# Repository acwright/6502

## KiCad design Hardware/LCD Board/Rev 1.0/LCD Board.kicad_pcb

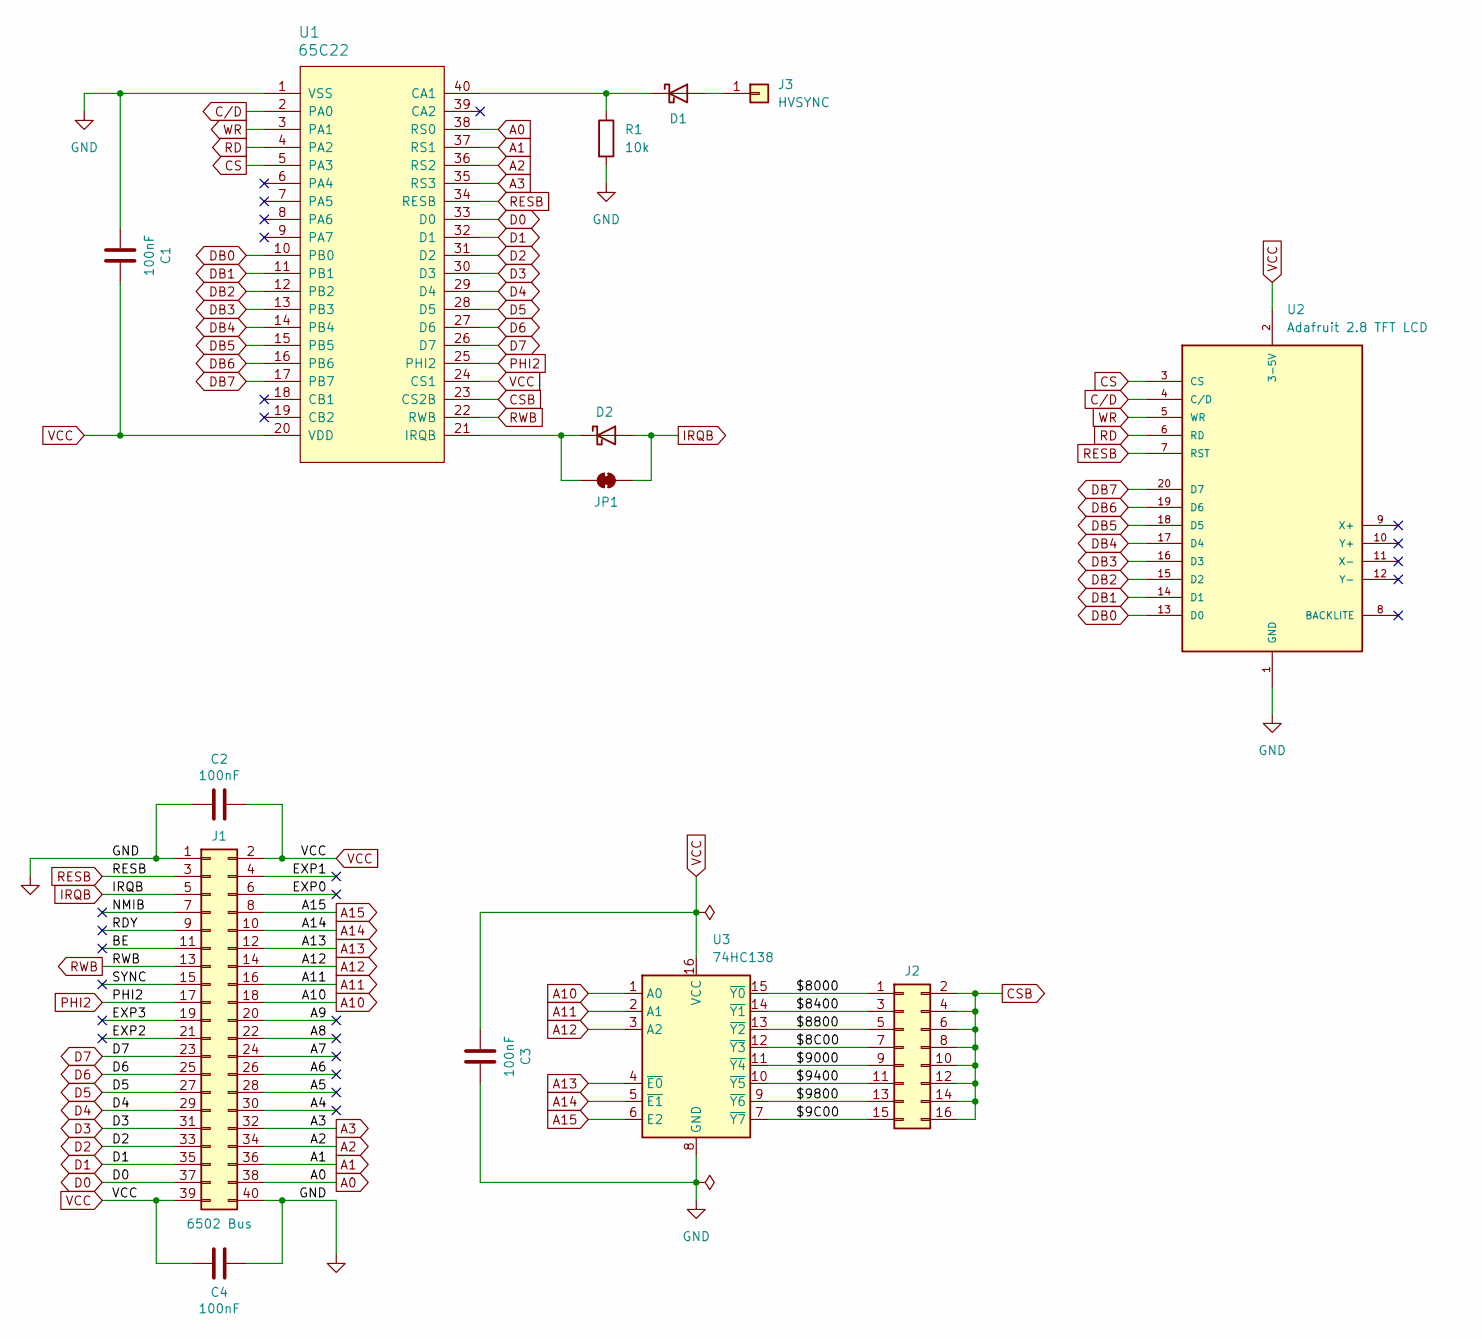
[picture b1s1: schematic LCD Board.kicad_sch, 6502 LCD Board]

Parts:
C1, C2, C3, C4: 100nF; C_Disc_D5.0mm_W2.5mm_P2.50mm
D1, D2: D_Schottky; D_DO-35_SOD27_P7.62mm_Horizontal
J1: 6502 Bus; 6502 Bus Connector
J2: Conn_02x08_Odd_Even; PinHeader_2x08_P2.54mm_Vertical
J3: HVSYNC; PinHeader_1x01_P2.54mm_Vertical
JP1: SolderJumper_2_Bridged; SolderJumper-2_P1.3mm_Bridged_RoundedPad1.0x1.5mm
R1: 10k; R_Axial_DIN0204_L3.6mm_D1.6mm_P5.08mm_Horizontal
U1: 65C22; DIP-40_W15.24mm_Socket_LongPads
U2: Adafruit 2.8 TFT LCD; PARTREV 2025-02-10
U3: 74HC138; DIP-16_W7.62mm_Socket_LongPads

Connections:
/$8C00: J2.7, U3.12 (~Y3)
/$9C00: J2.15, U3.7 (~Y7)
/$8000: J2.1, U3.15 (~Y0)
/$8400: J2.3, U3.14 (~Y1)
/$8800: J2.5, U3.13 (~Y2)
/$9000: J2.9, U3.11 (~Y4)
/$9400: J2.11, U3.10 (~Y5)
/$9800: J2.13, U3.9 (~Y6)
/A4: J1.30
/A5: J1.28
/A6: J1.26
/A7: J1.24
/A8: J1.22
/A9: J1.20
/BE: J1.11
/EXP0: J1.6
/EXP1: J1.4
/EXP2: J1.21
/EXP3: J1.19
/NMIB: J1.7
/RDY: J1.9
/SYNC: J1.15
A0: J1.38, U1.38 (RS0)
A1: J1.36, U1.37 (RS1)
A2: J1.34, U1.36 (RS2)
A3: J1.32, U1.35 (RS3)
A10: J1.18, U3.1 (A0)
A11: J1.16, U3.2 (A1)
A12: J1.14, U3.3 (A2)
A13: J1.12, U3.4 (~E0)
A14: J1.10, U3.5 (~E1)
A15: J1.8, U3.6 (E2)
CS: U1.5 (PA3), U2.3 (CS)
CSB: J2.2, J2.4, J2.6, J2.8, J2.10, J2.12, J2.14, J2.16, U1.23 (CS2B)
C/D: U1.2 (PA0), U2.4 (C/D)
D0: J1.37, U1.33 (D0)
D1: J1.35, U1.32 (D1)
D2: J1.33, U1.31 (D2)
D3: J1.31, U1.30 (D3)
D4: J1.29, U1.29 (D4)
D5: J1.27, U1.28 (D5)
D6: J1.25, U1.27 (D6)
D7: J1.23, U1.26 (D7)
DB0: U1.10 (PB0), U2.13 (D0)
DB1: U1.11 (PB1), U2.14 (D1)
DB2: U1.12 (PB2), U2.15 (D2)
DB3: U1.13 (PB3), U2.16 (D3)
DB4: U1.14 (PB4), U2.17 (D4)
DB5: U1.15 (PB5), U2.18 (D5)
DB6: U1.16 (PB6), U2.19 (D6)
DB7: U1.17 (PB7), U2.20 (D7)
GND: C1.1, C2.2, C3.2, C4.1, J1.1, J1.40, R1.2, U1.1 (VSS), U2.1 (GND), U3.8 (GND)
IRQB: D2.2 (A), J1.5, JP1.2 (B)
unnamed: D1.2 (A), J3.1
unnamed: D1.1 (K), R1.1, U1.40 (CA1)
unnamed: D2.1 (K), JP1.1 (A), U1.21 (IRQB)
PHI2: J1.17, U1.25 (PHI2)
RD: U1.4 (PA2), U2.6 (RD)
RESB: J1.3, U1.34 (RESB), U2.7 (RST)
RWB: J1.13, U1.22 (RWB)
VCC: C1.2, C2.1, C3.1, C4.2, J1.2, J1.39, U1.20 (VDD), U1.24 (CS1), U2.2 (3-5V), U3.16 (VCC)
WR: U1.3 (PA1), U2.5 (WR)

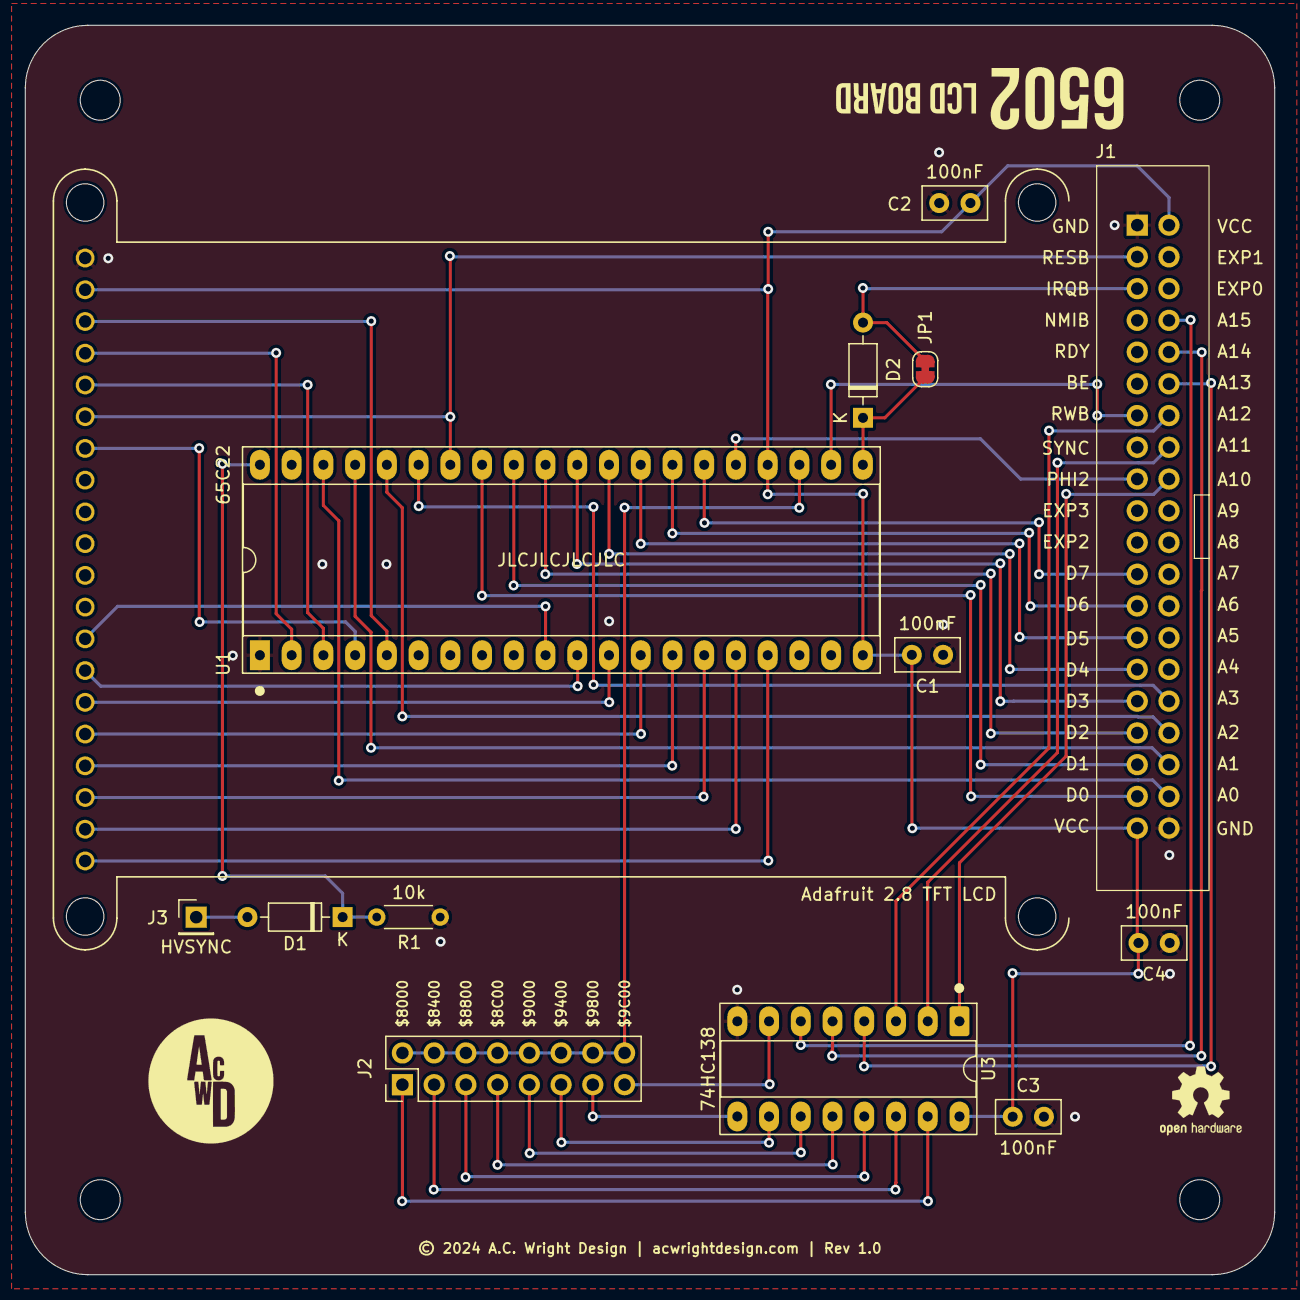
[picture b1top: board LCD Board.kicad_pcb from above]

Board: 2 copper layers, 100.0 x 100.0 mm, 18 parts (0 on the bottom side), 48 nets.

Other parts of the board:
H1, H2, H3, H4: MountingHole; MountingHole_3.2mm_M3

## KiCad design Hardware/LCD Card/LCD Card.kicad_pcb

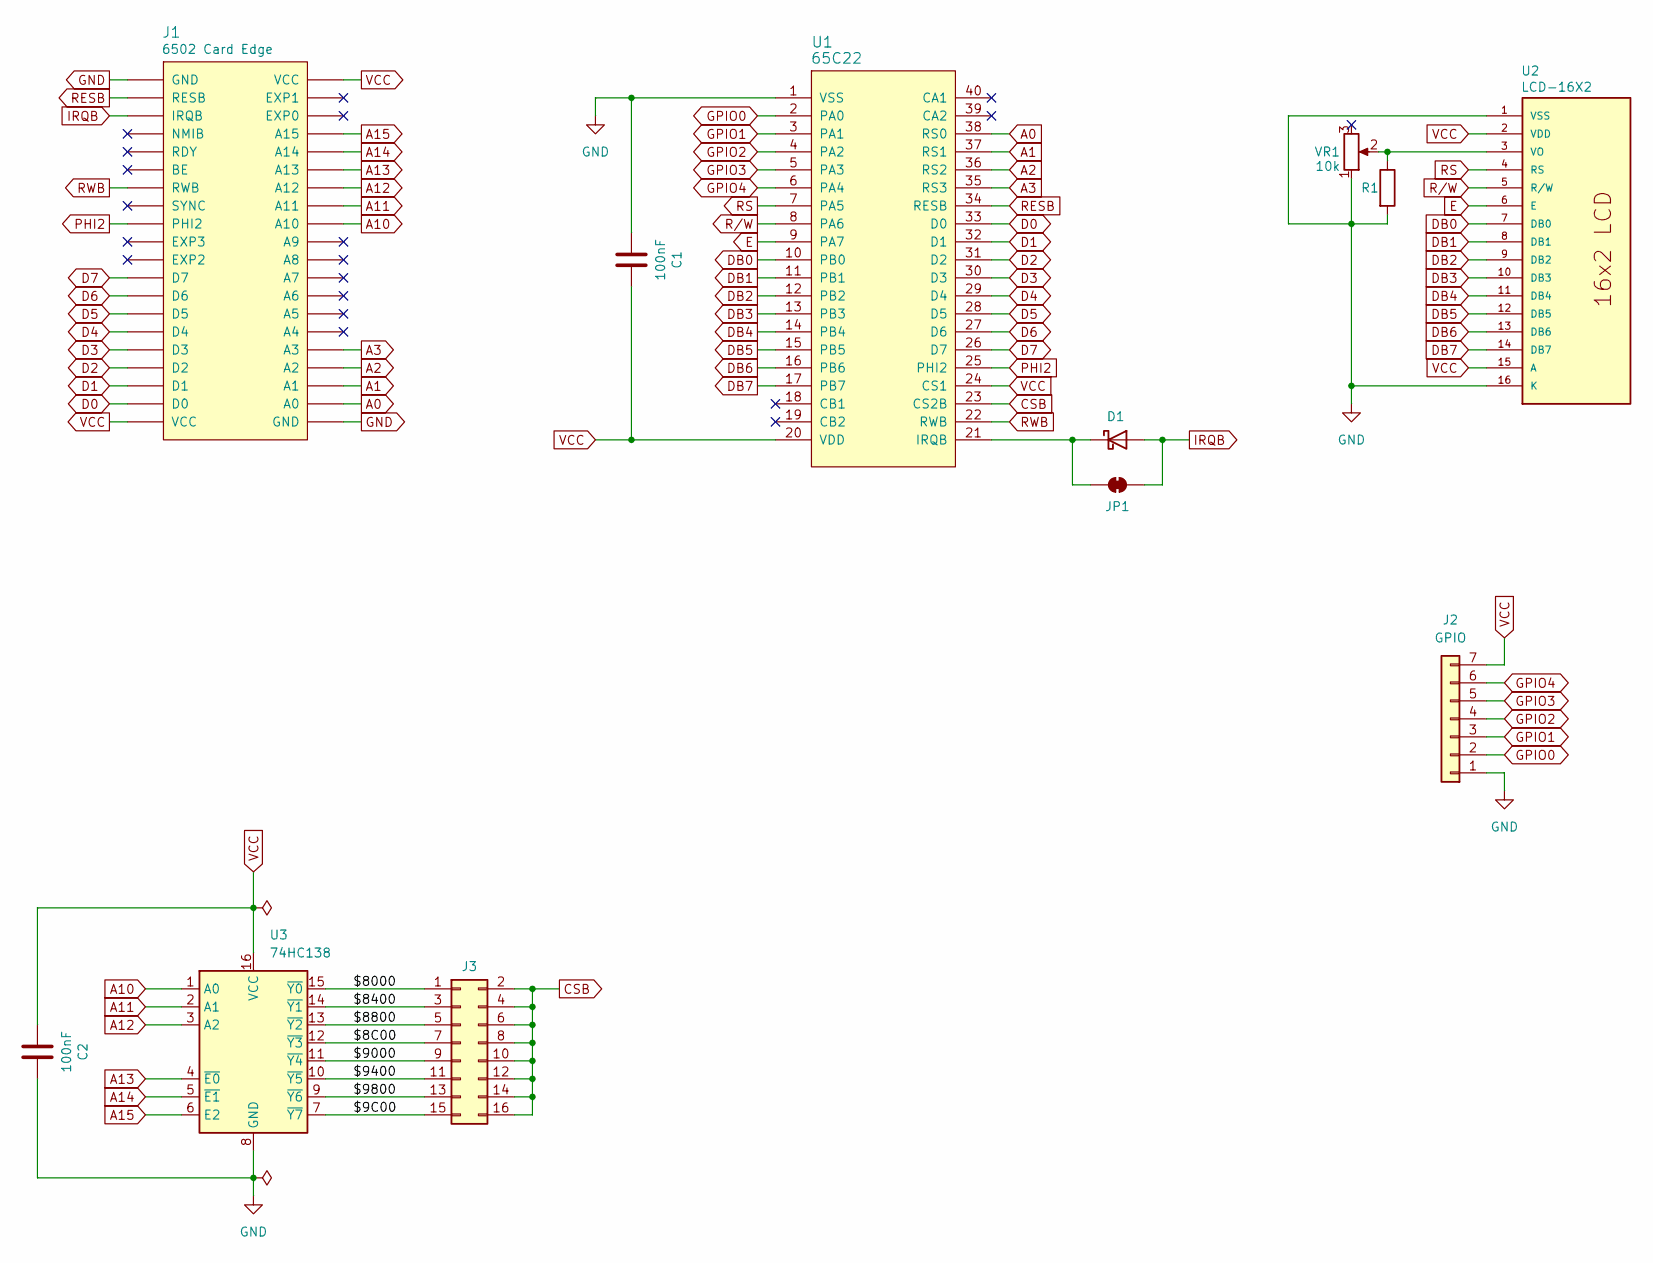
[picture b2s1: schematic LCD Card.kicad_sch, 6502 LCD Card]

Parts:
C1, C2: 100nF; C_0805_2012Metric; LCSC C49678
D1: D_Schottky; D_DO-35_SOD27_P7.62mm_Horizontal
J1: 6502 Card Edge
J2: GPIO; PinHeader_1x07_P2.54mm_Horizontal
J3: Conn_02x08_Odd_Even; PinHeader_2x08_P2.54mm_Vertical
JP1: SolderJumper_2_Bridged; SolderJumper-2_P1.3mm_Bridged_RoundedPad1.0x1.5mm
R1: R; R_Axial_DIN0204_L3.6mm_D1.6mm_P5.08mm_Horizontal
U1: 65C22; DIP-40_W15.24mm_Socket_LongPads
U2: LCD-16X2; PARTREV N/A
U3: 74HC138; SOIC-16_3.9x9.9mm_P1.27mm; LCSC C5602
VR1: 10k; 3386F-1-103TLF

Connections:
/$8C00: J3.7, U3.12 (~Y3)
/$9C00: J3.15, U3.7 (~Y7)
/$8000: J3.1, U3.15 (~Y0)
/$8400: J3.3, U3.14 (~Y1)
/$8800: J3.5, U3.13 (~Y2)
/$9000: J3.9, U3.11 (~Y4)
/$9400: J3.11, U3.10 (~Y5)
/$9800: J3.13, U3.9 (~Y6)
A0: J1.A0, U1.38 (RS0)
A1: J1.A1, U1.37 (RS1)
A2: J1.A2, U1.36 (RS2)
A3: J1.A3, U1.35 (RS3)
A10: J1.A10, U3.1 (A0)
A11: J1.A11, U3.2 (A1)
A12: J1.A12, U3.3 (A2)
A13: J1.A13, U3.4 (~E0)
A14: J1.A14, U3.5 (~E1)
A15: J1.A15, U3.6 (E2)
CSB: J3.2, J3.4, J3.6, J3.8, J3.10, J3.12, J3.14, J3.16, U1.23 (CS2B)
D0: J1.D0, U1.33 (D0)
D1: J1.D1, U1.32 (D1)
D2: J1.D2, U1.31 (D2)
D3: J1.D3, U1.30 (D3)
D4: J1.D4, U1.29 (D4)
D5: J1.D5, U1.28 (D5)
D6: J1.D6, U1.27 (D6)
D7: J1.D7, U1.26 (D7)
DB0: U1.10 (PB0), U2.7 (DB0)
DB1: U1.11 (PB1), U2.8 (DB1)
DB2: U1.12 (PB2), U2.9 (DB2)
DB3: U1.13 (PB3), U2.10 (DB3)
DB4: U1.14 (PB4), U2.11 (DB4)
DB5: U1.15 (PB5), U2.12 (DB5)
DB6: U1.16 (PB6), U2.13 (DB6)
DB7: U1.17 (PB7), U2.14 (DB7)
E: U1.9 (PA7), U2.6 (E)
GND: C1.1, C2.2, J1.GND, J2.1, R1.2, U1.1 (VSS), U2.1 (VSS), U2.16 (K), U3.8 (GND), VR1.1
GPIO0: J2.2, U1.2 (PA0)
GPIO1: J2.3, U1.3 (PA1)
GPIO2: J2.4, U1.4 (PA2)
GPIO3: J2.5, U1.5 (PA3)
GPIO4: J2.6, U1.6 (PA4)
IRQB: D1.2 (A), J1.IRQB, JP1.2 (B)
unnamed: D1.1 (K), JP1.1 (A), U1.21 (IRQB)
unnamed: R1.1, U2.3 (VO), VR1.2
PHI2: J1.PHI2, U1.25 (PHI2)
RESB: J1.RESB, U1.34 (RESB)
RS: U1.7 (PA5), U2.4 (RS)
RWB: J1.RWB, U1.22 (RWB)
R/W: U1.8 (PA6), U2.5 (R/W)
VCC: C1.2, C2.1, J1.VCC, J2.7, U1.20 (VDD), U1.24 (CS1), U2.2 (VDD), U2.15 (A), U3.16 (VCC)

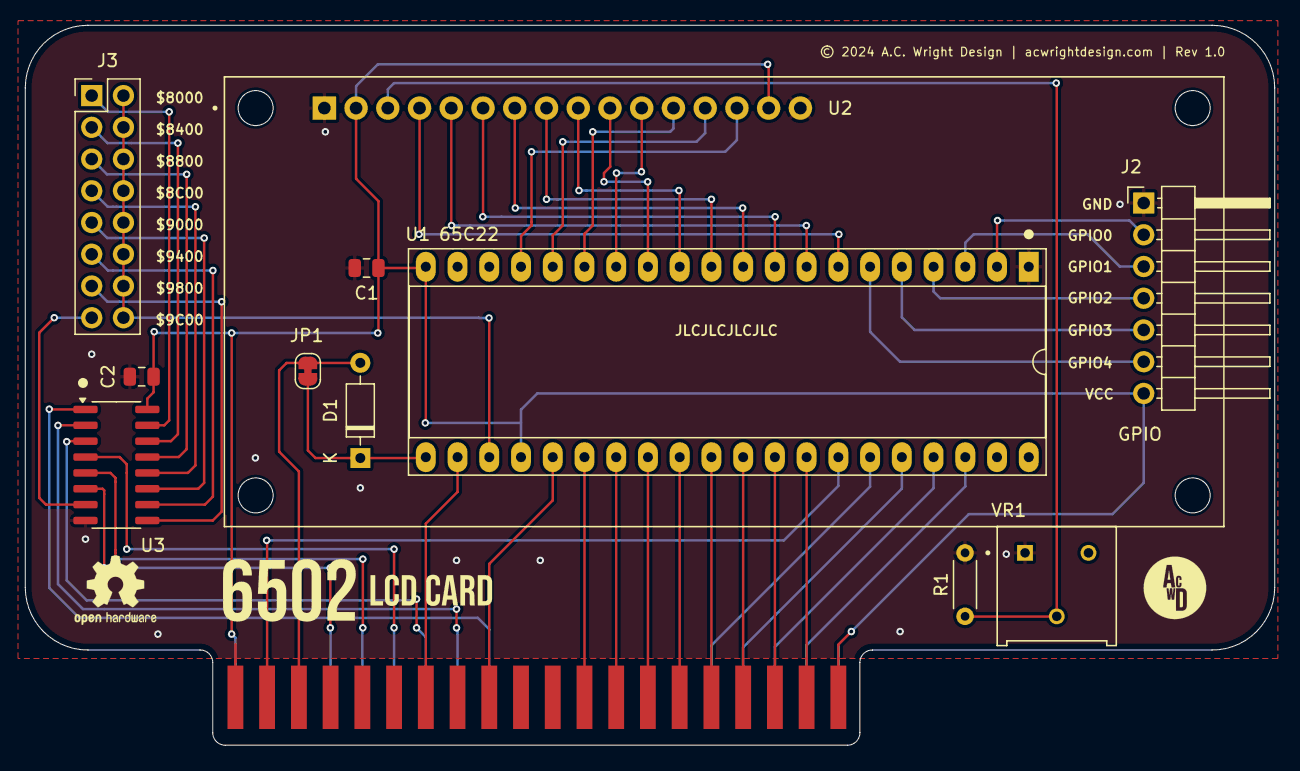
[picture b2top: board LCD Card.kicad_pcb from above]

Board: 2 copper layers, 100.0 x 57.6 mm, 12 parts (0 on the bottom side), 51 nets.

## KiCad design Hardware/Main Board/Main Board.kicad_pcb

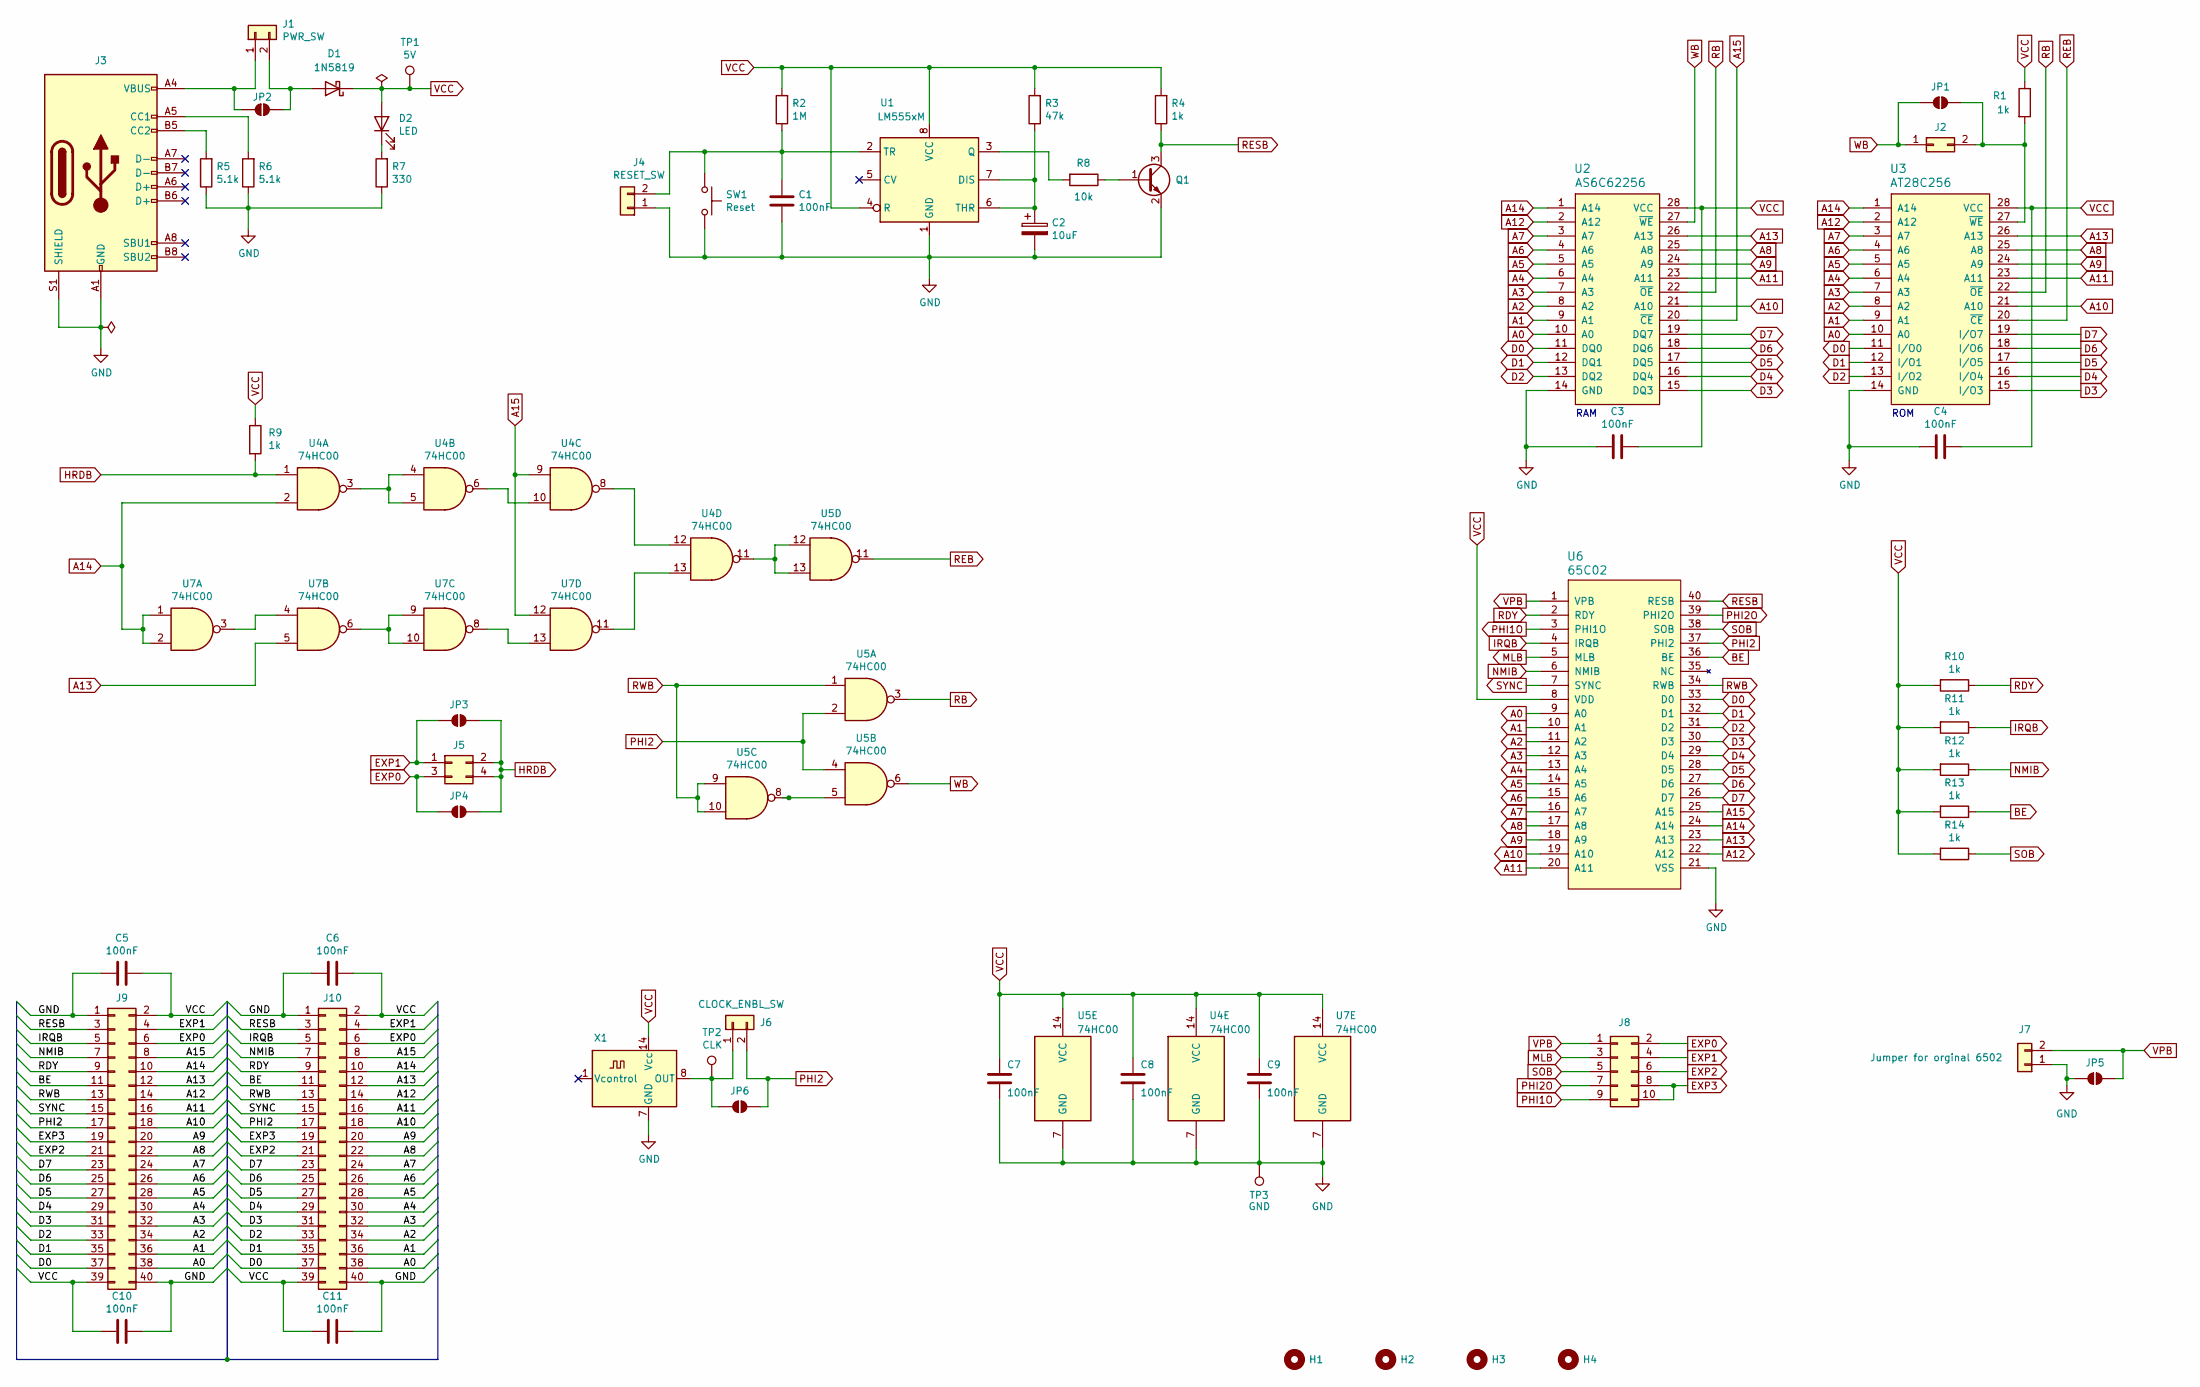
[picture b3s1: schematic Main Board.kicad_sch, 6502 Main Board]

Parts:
C1, C3, C4, C5, C6, C7, C8, C9, C10, C11: 100nF; C_0805_2012Metric; LCSC C49678
C2: 10uF; C_1206_3216Metric; LCSC C7171
D1: 1N5819; D_SOD-323F; LCSC C191023
D2: LED; LED_0805_2012Metric; LCSC C2297
H1, H2, H3, H4: MountingHole; MountingHole_3.2mm_M3
J1: PWR_SW; JST_XH_B2B-XH-A_1x02_P2.50mm_Vertical; Digikey 455-2247-ND
J2: Conn_02x01; PinHeader_1x02_P2.54mm_Vertical
J3: USB_C_Receptacle_USB2.0; USB_C_Receptacle_HRO_TYPE-C-31-M-12; LCSC C2988369
J4: RESET_SW; JST_XH_B2B-XH-A_1x02_P2.50mm_Vertical; Digikey 455-2247-ND
J5: Conn_02x02_Odd_Even; PinHeader_2x02_P2.54mm_Vertical
J6: CLOCK_ENBL_SW; JST_XH_B2B-XH-A_1x02_P2.50mm_Vertical; Digikey 455-2247-ND
J7: Conn_01x02; PinHeader_1x02_P2.54mm_Vertical
J8: Conn_02x05_Odd_Even; PinHeader_2x05_P2.54mm_Vertical
J9: Conn_02x20_Odd_Even; RHDR40W82P485X254_2X20_5740X93; Mouser 571-5-5530843-4
J10: Conn_02x20_Odd_Even; PinHeader_2x20_P2.54mm_Vertical
JP1, JP2, JP3, JP4, JP5, JP6: SolderJumper_2_Open; SolderJumper-2_P1.3mm_Open_RoundedPad1.0x1.5mm
Q1: Q_NPN_BEC; SOT-23; LCSC C2150
R1, R4, R9, R10, R11, R12, R13, R14: 1k; R_0805_2012Metric; LCSC C17513
R2: 1M; R_0805_2012Metric; LCSC C17514
R3: 47k; R_0805_2012Metric; LCSC C17713
R5, R6: 5.1k; R_0805_2012Metric; LCSC C27834
R7: 330; R_0805_2012Metric; LCSC C17630
R8: 10k; R_0805_2012Metric; LCSC C17414
SW1: Reset; SW_TS-1187A-B-A-B; LCSC C318884
TP1: 5V; TestPoint_Pad_1.0x1.0mm
TP2: CLK; TestPoint_Pad_1.0x1.0mm
TP3: GND; TestPoint_Pad_1.0x1.0mm
U1: LM555xM; SOIC-8_3.9x4.9mm_P1.27mm; LCSC C7593
U2: AS6C62256; DIP-28_W15.24mm_Socket_LongPads
U3: AT28C256; DIP_Socket-28_W11.9_W12.7_W15.24_W17.78_W18.5_3M_228-1277-0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
U4, U5, U7: 74HC00; SOIC-14_3.9x8.7mm_P1.27mm; LCSC C5586
U6: 65C02; DIP-40_W15.24mm_Socket_LongPads
X1: OCXO-14; Oscillator_DIP-14

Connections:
A0: J9.38, J10.38, U2.10 (A0), U3.10 (A0), U6.9 (A0)
A1: J9.36, J10.36, U2.9 (A1), U3.9 (A1), U6.10 (A1)
A2: J9.34, J10.34, U2.8 (A2), U3.8 (A2), U6.11 (A2)
A3: J9.32, J10.32, U2.7 (A3), U3.7 (A3), U6.12 (A3)
A4: J9.30, J10.30, U2.6 (A4), U3.6 (A4), U6.13 (A4)
A5: J9.28, J10.28, U2.5 (A5), U3.5 (A5), U6.14 (A5)
A6: J9.26, J10.26, U2.4 (A6), U3.4 (A6), U6.15 (A6)
A7: J9.24, J10.24, U2.3 (A7), U3.3 (A7), U6.16 (A7)
A8: J9.22, J10.22, U2.25 (A8), U3.25 (A8), U6.17 (A8)
A9: J9.20, J10.20, U2.24 (A9), U3.24 (A9), U6.18 (A9)
A10: J9.18, J10.18, U2.21 (A10), U3.21 (A10), U6.19 (A10)
A11: J9.16, J10.16, U2.23 (A11), U3.23 (A11), U6.20 (A11)
A12: J9.14, J10.14, U2.2 (A12), U3.2 (A12), U6.22 (A12)
A13: J9.12, J10.12, U2.26 (A13), U3.26 (A13), U6.23 (A13), U7.5
A14: J9.10, J10.10, U2.1 (A14), U3.1 (A14), U4.2, U6.24 (A14), U7.1, U7.2
A15: J9.8, J10.8, U2.20 (~CE), U4.9, U6.25 (A15), U7.12
BE: J9.11, J10.11, R13.1, U6.36 (BE)
D0: J9.37, J10.37, U2.11 (DQ0), U3.11 (I/O0), U6.33 (D0)
D1: J9.35, J10.35, U2.12 (DQ1), U3.12 (I/O1), U6.32 (D1)
D2: J9.33, J10.33, U2.13 (DQ2), U3.13 (I/O2), U6.31 (D2)
D3: J9.31, J10.31, U2.15 (DQ3), U3.15 (I/O3), U6.30 (D3)
D4: J9.29, J10.29, U2.16 (DQ4), U3.16 (I/O4), U6.29 (D4)
D5: J9.27, J10.27, U2.17 (DQ5), U3.17 (I/O5), U6.28 (D5)
D6: J9.25, J10.25, U2.18 (DQ6), U3.18 (I/O6), U6.27 (D6)
D7: J9.23, J10.23, U2.19 (DQ7), U3.19 (I/O7), U6.26 (D7)
EXP0: J5.3, J8.2, J9.6, J10.6, JP4.1 (A)
EXP1: J5.1, J8.4, J9.4, J10.4, JP3.1 (A)
EXP2: J8.6, J9.21, J10.21
EXP3: J8.8, J8.10, J9.19, J10.19
GND: C1.2, C2.2, C3.2, C4.2, C5.2, C6.2, C7.2, C8.2, C9.2, C10.1, C11.1, J3.A1 (GND), J3.A12 (GND), J3.B1 (GND), J3.B12 (GND), J3.S1 (SHIELD), J4.1, J7.1, J9.1, J9.40, J10.1, J10.40, JP5.1 (A), Q1.2 (E), R5.1, R6.1, R7.1, SW1.2, TP3.1, U1.1 (GND), U2.14 (GND), U3.14 (GND), U4.7 (GND), U5.7 (GND), U6.21 (VSS), U7.7 (GND), X1.7 (GND)
HRDB: J5.2, J5.4, JP3.2 (B), JP4.2 (B), R9.2, U4.1
IRQB: J9.5, J10.5, R11.1, U6.4 (IRQB)
MLB: J8.3, U6.5 (MLB)
NMIB: J9.7, J10.7, R12.1, U6.6 (NMIB)
unnamed: D1.2 (A), J1.2, JP2.2 (B)
unnamed: D2.1 (K), R7.2
unnamed: J1.1, J3.A4 (VBUS), J3.A9 (VBUS), J3.B4 (VBUS), J3.B9 (VBUS), JP2.1 (A)
unnamed: J2.2, JP1.2 (B), R1.2, U3.27 (~WE)
unnamed: J3.A5 (CC1), R6.2
unnamed: J3.B5 (CC2), R5.2
unnamed: C1.1, J4.2, R2.1, SW1.1, U1.2 (TR)
unnamed: J6.1, JP6.1 (A), TP2.1, X1.8 (OUT)
unnamed: Q1.1 (B), R8.1
unnamed: C2.1, R3.1, U1.6 (THR), U1.7 (DIS)
unnamed: R8.2, U1.3 (Q)
unnamed: U4.3, U4.4, U4.5
unnamed: U4.6, U4.10
unnamed: U4.11, U5.12, U5.13
unnamed: U4.8, U4.12
unnamed: U4.13, U7.11
unnamed: U5.5, U5.8
unnamed: U7.3, U7.4
unnamed: U7.6, U7.9, U7.10
unnamed: U7.8, U7.13
PHI1O: J8.9, U6.3 (PHI1O)
PHI2: J6.2, J9.17, J10.17, JP6.2 (B), U5.2, U5.4, U6.37 (PHI2)
PHI2O: J8.7, U6.39 (PHI2O)
RB: U2.22 (~OE), U3.22 (~OE), U5.3
RDY: J9.9, J10.9, R10.1, U6.2 (RDY)
REB: U3.20 (~CE), U5.11
RESB: J9.3, J10.3, Q1.3 (C), R4.1, U6.40 (RESB)
RWB: J9.13, J10.13, U5.1, U5.9, U5.10, U6.34 (RWB)
SOB: J8.5, R14.1, U6.38 (SOB)
SYNC: J9.15, J10.15, U6.7 (SYNC)
VCC: C3.1, C4.1, C5.1, C6.1, C7.1, C8.1, C9.1, C10.2, C11.2, D1.1 (K), D2.2 (A), J9.2, J9.39, J10.2, J10.39, R1.1, R2.2, R3.2, R4.2, R9.1, R10.2, R11.2, R12.2, R13.2, R14.2, TP1.1, U1.4 (R), U1.8 (VCC), U2.28 (VCC), U3.28 (VCC), U4.14 (VCC), U5.14 (VCC), U6.8 (VDD), U7.14 (VCC), X1.14 (Vcc)
VPB: J7.2, J8.1, JP5.2 (B), U6.1 (VPB)
WB: J2.1, JP1.1 (A), U2.27 (~WE), U5.6

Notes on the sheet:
ROM
RAM

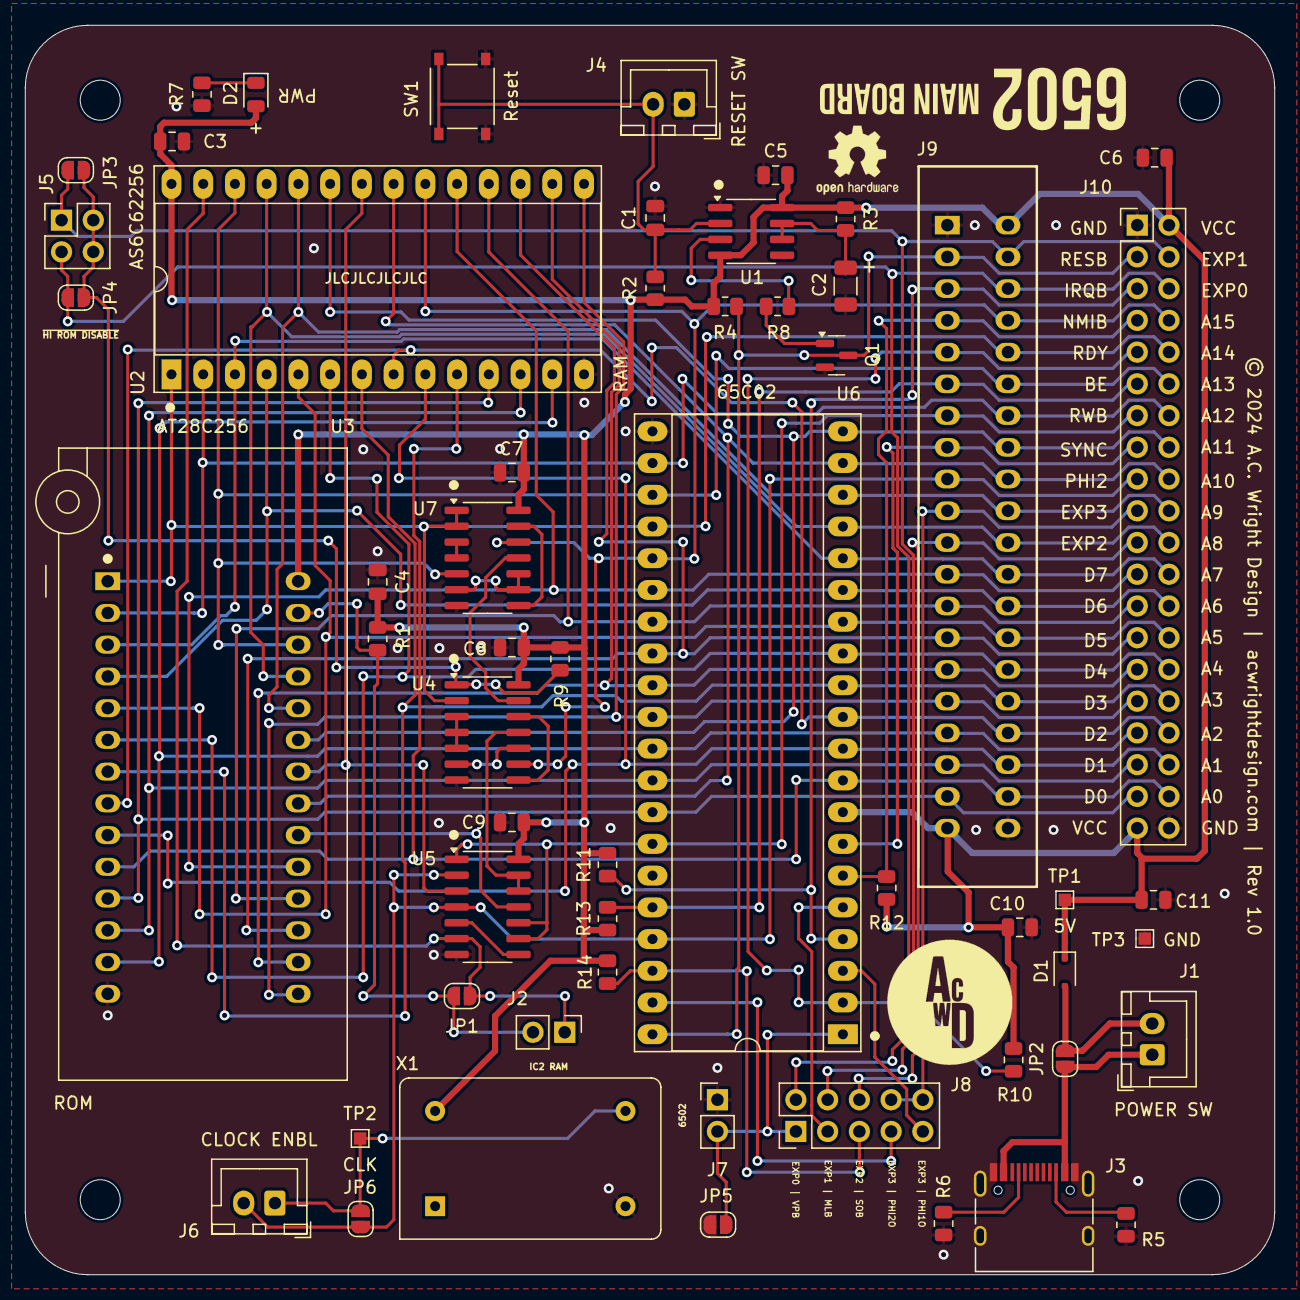
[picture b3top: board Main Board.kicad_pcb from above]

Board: 2 copper layers, 100.0 x 100.0 mm, 60 parts (0 on the bottom side), 67 nets.

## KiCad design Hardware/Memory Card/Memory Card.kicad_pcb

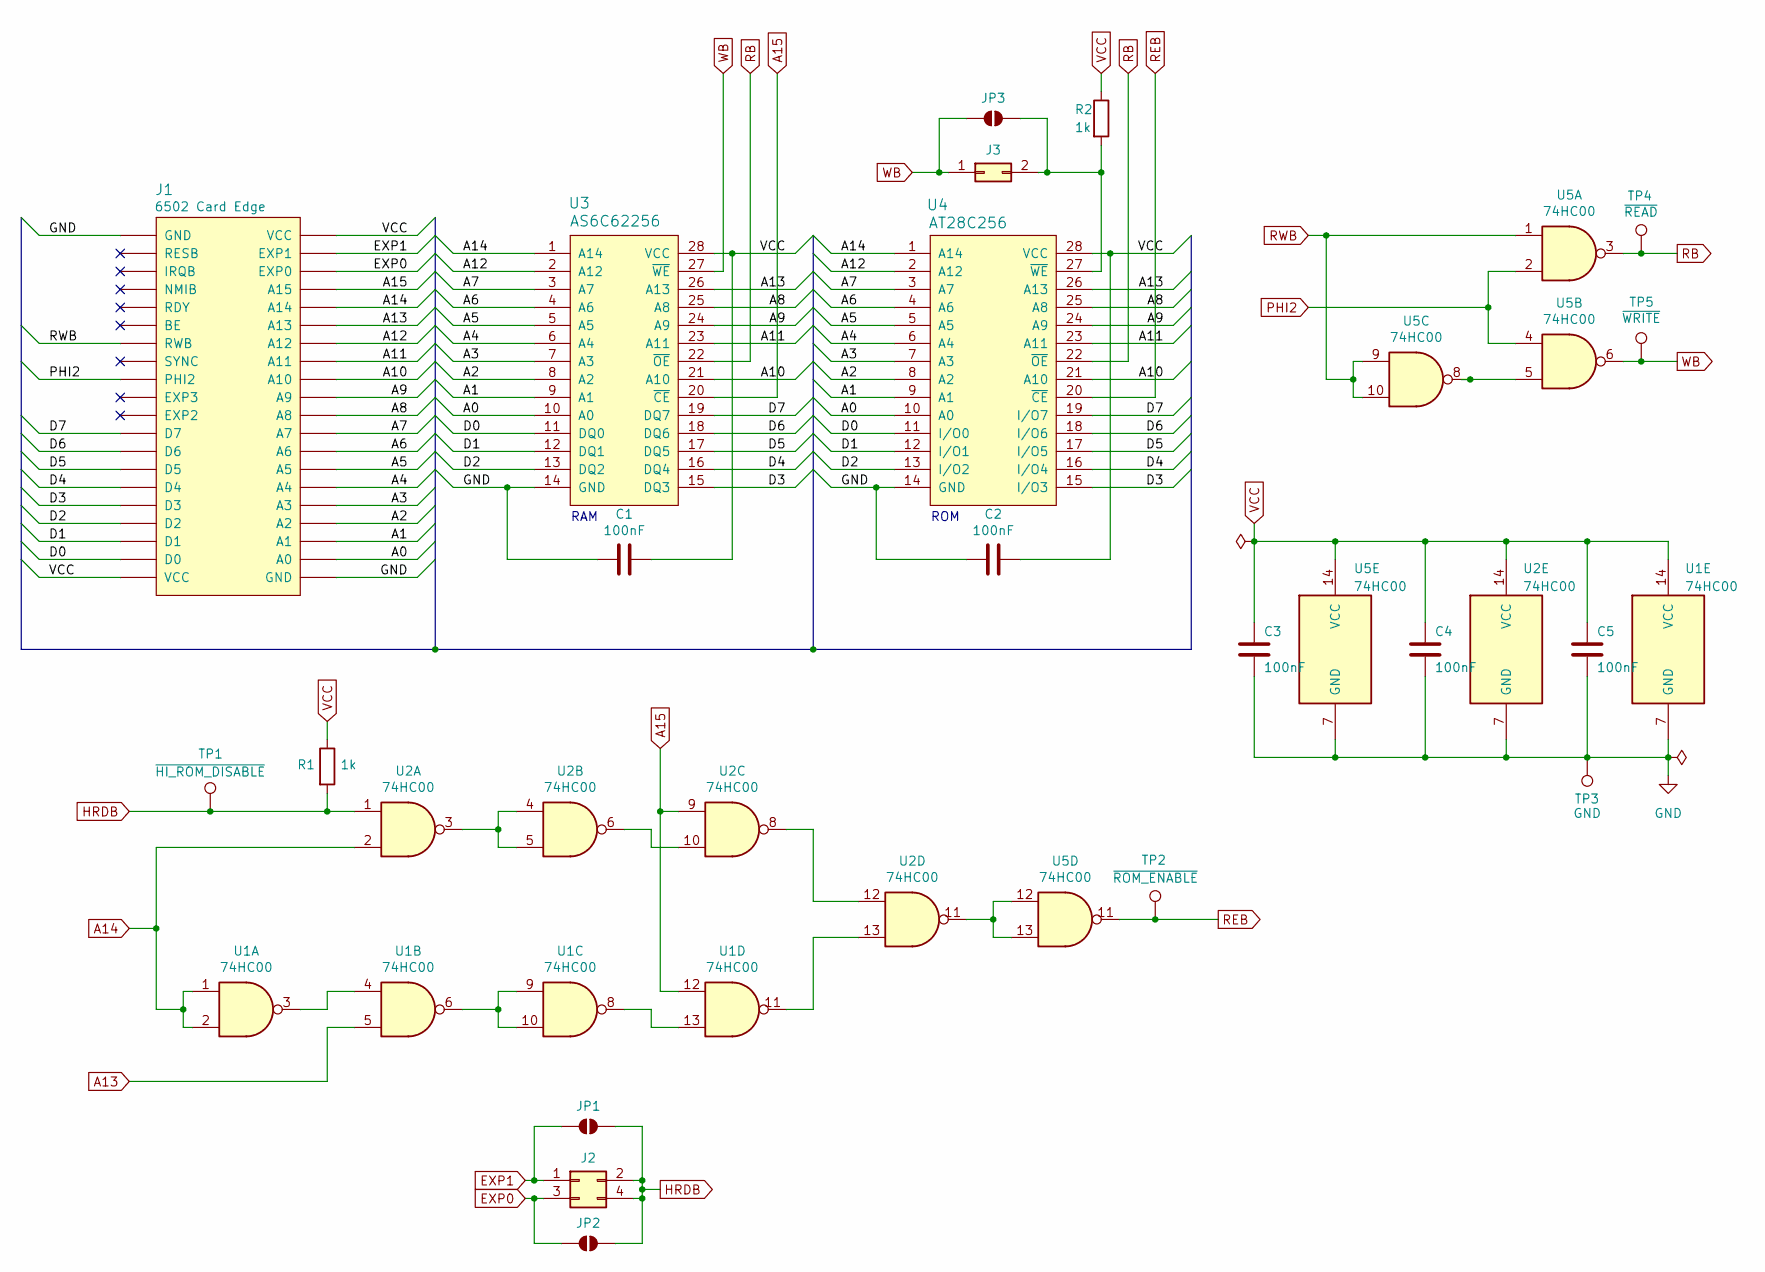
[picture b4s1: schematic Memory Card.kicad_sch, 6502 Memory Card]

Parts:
C1, C2, C3, C4, C5: 100nF; C_0805_2012Metric; LCSC C49678
J1: 6502 Card Edge
J2: Conn_02x02_Odd_Even; PinHeader_2x02_P2.54mm_Vertical
J3: Conn_02x01; PinHeader_1x02_P2.54mm_Vertical
JP1, JP2, JP3: SolderJumper_2_Open; SolderJumper-2_P1.3mm_Open_RoundedPad1.0x1.5mm
R1, R2: 1k; R_0805_2012Metric; LCSC C17513
TP1: ~{HI_ROM_DISABLE}; TestPoint_Pad_1.0x1.0mm
TP2: ~{ROM_ENABLE}; TestPoint_Pad_1.0x1.0mm
TP3: GND; TestPoint_Pad_1.0x1.0mm
TP4: ~{READ}; TestPoint_Pad_1.0x1.0mm
TP5: ~{WRITE}; TestPoint_Pad_1.0x1.0mm
U1, U2, U5: 74HC00; SOIC-14_3.9x8.7mm_P1.27mm; LCSC C5586
U3: AS6C62256; DIP-28_W15.24mm_Socket_LongPads
U4: AT28C256; DIP-28_W15.24mm_Socket_LongPads

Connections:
/A0: J1.A0, U3.10 (A0), U4.10 (A0)
/A1: J1.A1, U3.9 (A1), U4.9 (A1)
/A2: J1.A2, U3.8 (A2), U4.8 (A2)
/A3: J1.A3, U3.7 (A3), U4.7 (A3)
/A4: J1.A4, U3.6 (A4), U4.6 (A4)
/A5: J1.A5, U3.5 (A5), U4.5 (A5)
/A6: J1.A6, U3.4 (A6), U4.4 (A6)
/A7: J1.A7, U3.3 (A7), U4.3 (A7)
/A8: J1.A8, U3.25 (A8), U4.25 (A8)
/A9: J1.A9, U3.24 (A9), U4.24 (A9)
/A10: J1.A10, U3.21 (A10), U4.21 (A10)
/A11: J1.A11, U3.23 (A11), U4.23 (A11)
/A12: J1.A12, U3.2 (A12), U4.2 (A12)
/D0: J1.D0, U3.11 (DQ0), U4.11 (I/O0)
/D1: J1.D1, U3.12 (DQ1), U4.12 (I/O1)
/D2: J1.D2, U3.13 (DQ2), U4.13 (I/O2)
/D3: J1.D3, U3.15 (DQ3), U4.15 (I/O3)
/D4: J1.D4, U3.16 (DQ4), U4.16 (I/O4)
/D5: J1.D5, U3.17 (DQ5), U4.17 (I/O5)
/D6: J1.D6, U3.18 (DQ6), U4.18 (I/O6)
/D7: J1.D7, U3.19 (DQ7), U4.19 (I/O7)
A13: J1.A13, U1.5, U3.26 (A13), U4.26 (A13)
A14: J1.A14, U1.1, U1.2, U2.2, U3.1 (A14), U4.1 (A14)
A15: J1.A15, U1.12, U2.9, U3.20 (~CE)
EXP0: J1.EXP0, J2.3, JP2.1 (A)
EXP1: J1.EXP1, J2.1, JP1.1 (A)
GND: C1.2, C2.2, C3.2, C4.2, C5.2, J1.GND, TP3.1, U1.7 (GND), U2.7 (GND), U3.14 (GND), U4.14 (GND), U5.7 (GND)
HRDB: J2.2, J2.4, JP1.2 (B), JP2.2 (B), R1.2, TP1.1, U2.1
unnamed: J3.2, JP3.2 (B), R2.2, U4.27 (~WE)
unnamed: U1.3, U1.4
unnamed: U1.6, U1.9, U1.10
unnamed: U1.11, U2.13
unnamed: U1.8, U1.13
unnamed: U2.3, U2.4, U2.5
unnamed: U2.6, U2.10
unnamed: U2.11, U5.12, U5.13
unnamed: U2.8, U2.12
unnamed: U5.5, U5.8
PHI2: J1.PHI2, U5.2, U5.4
RB: TP4.1, U3.22 (~OE), U4.22 (~OE), U5.3
REB: TP2.1, U4.20 (~CE), U5.11
RWB: J1.RWB, U5.1, U5.9, U5.10
VCC: C1.1, C2.1, C3.1, C4.1, C5.1, J1.VCC, R1.1, R2.1, U1.14 (VCC), U2.14 (VCC), U3.28 (VCC), U4.28 (VCC), U5.14 (VCC)
WB: J3.1, JP3.1 (A), TP5.1, U3.27 (~WE), U5.6

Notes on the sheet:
RAM
ROM

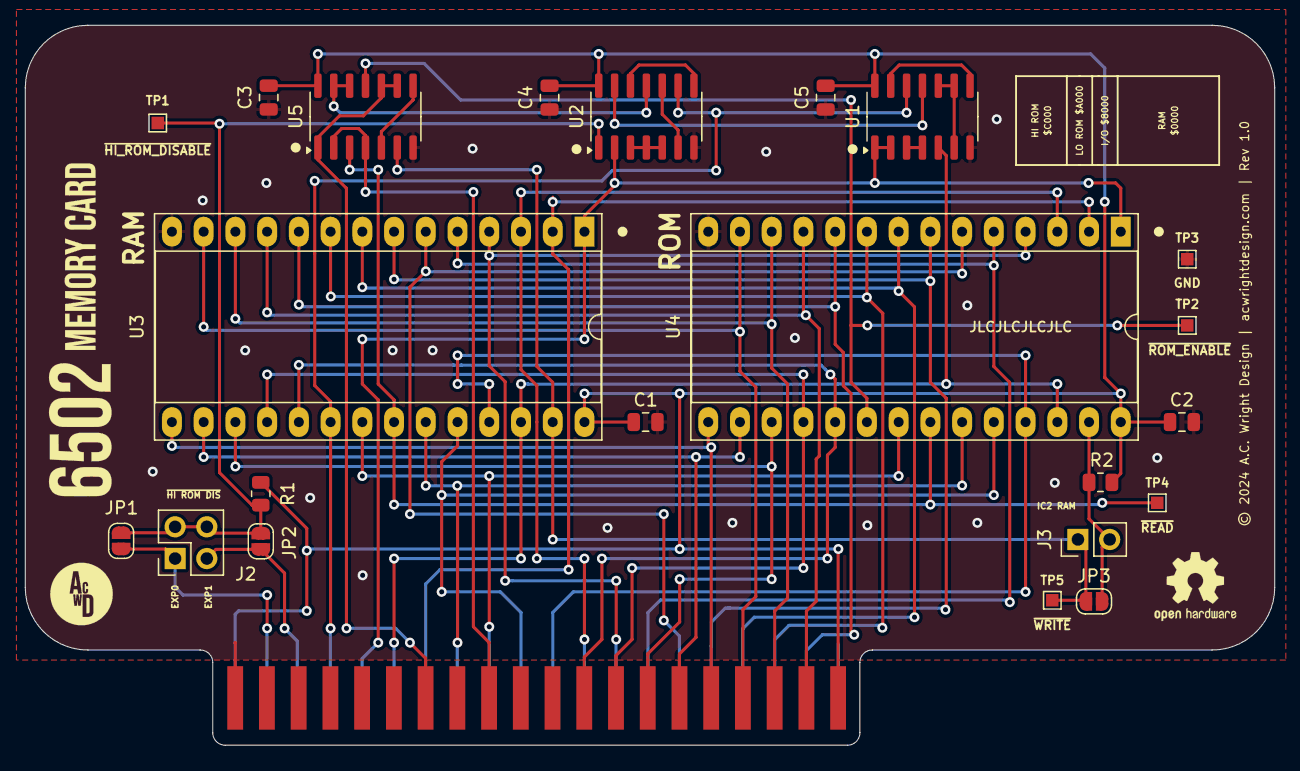
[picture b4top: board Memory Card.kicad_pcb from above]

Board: 2 copper layers, 100.0 x 57.6 mm, 23 parts (0 on the bottom side), 44 nets.

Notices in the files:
Hardware/LCD Board/Rev 1.0/LCD Board.kicad_pcb:
© 2024 A.C. Wright Design | acwrightdesign.com | Rev 1.0
